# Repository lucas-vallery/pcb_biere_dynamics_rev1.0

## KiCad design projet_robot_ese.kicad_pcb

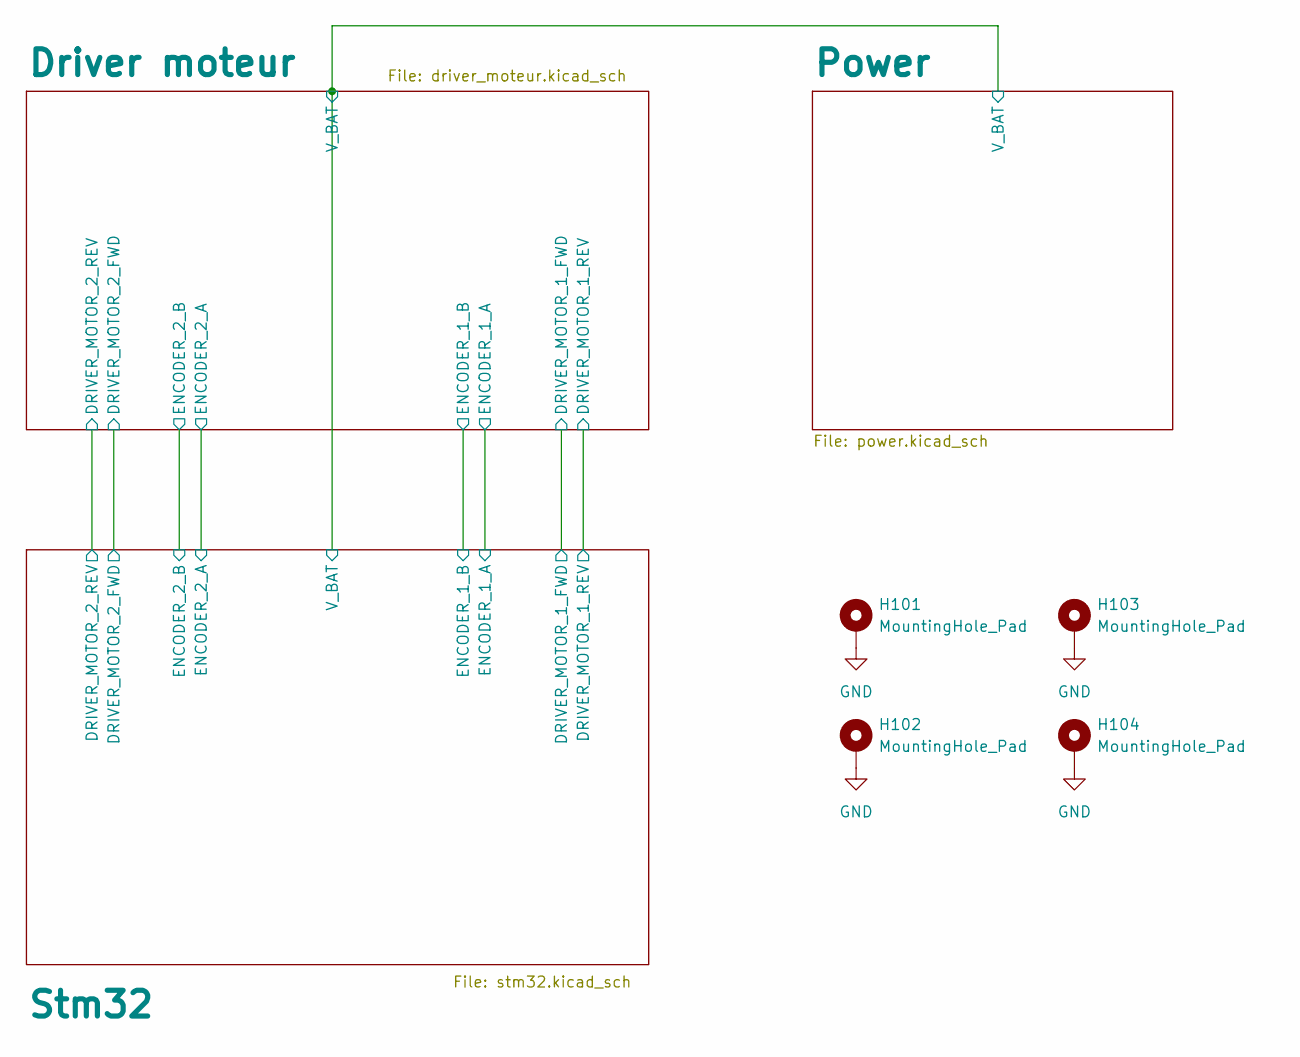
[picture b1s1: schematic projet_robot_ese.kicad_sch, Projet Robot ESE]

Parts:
H101, H102, H103, H104: MountingHole_Pad; MountingHole_3.2mm_M3_Pad_Via

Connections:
GND: H101.1, H102.1, H103.1, H104.1; also elsewhere on the board

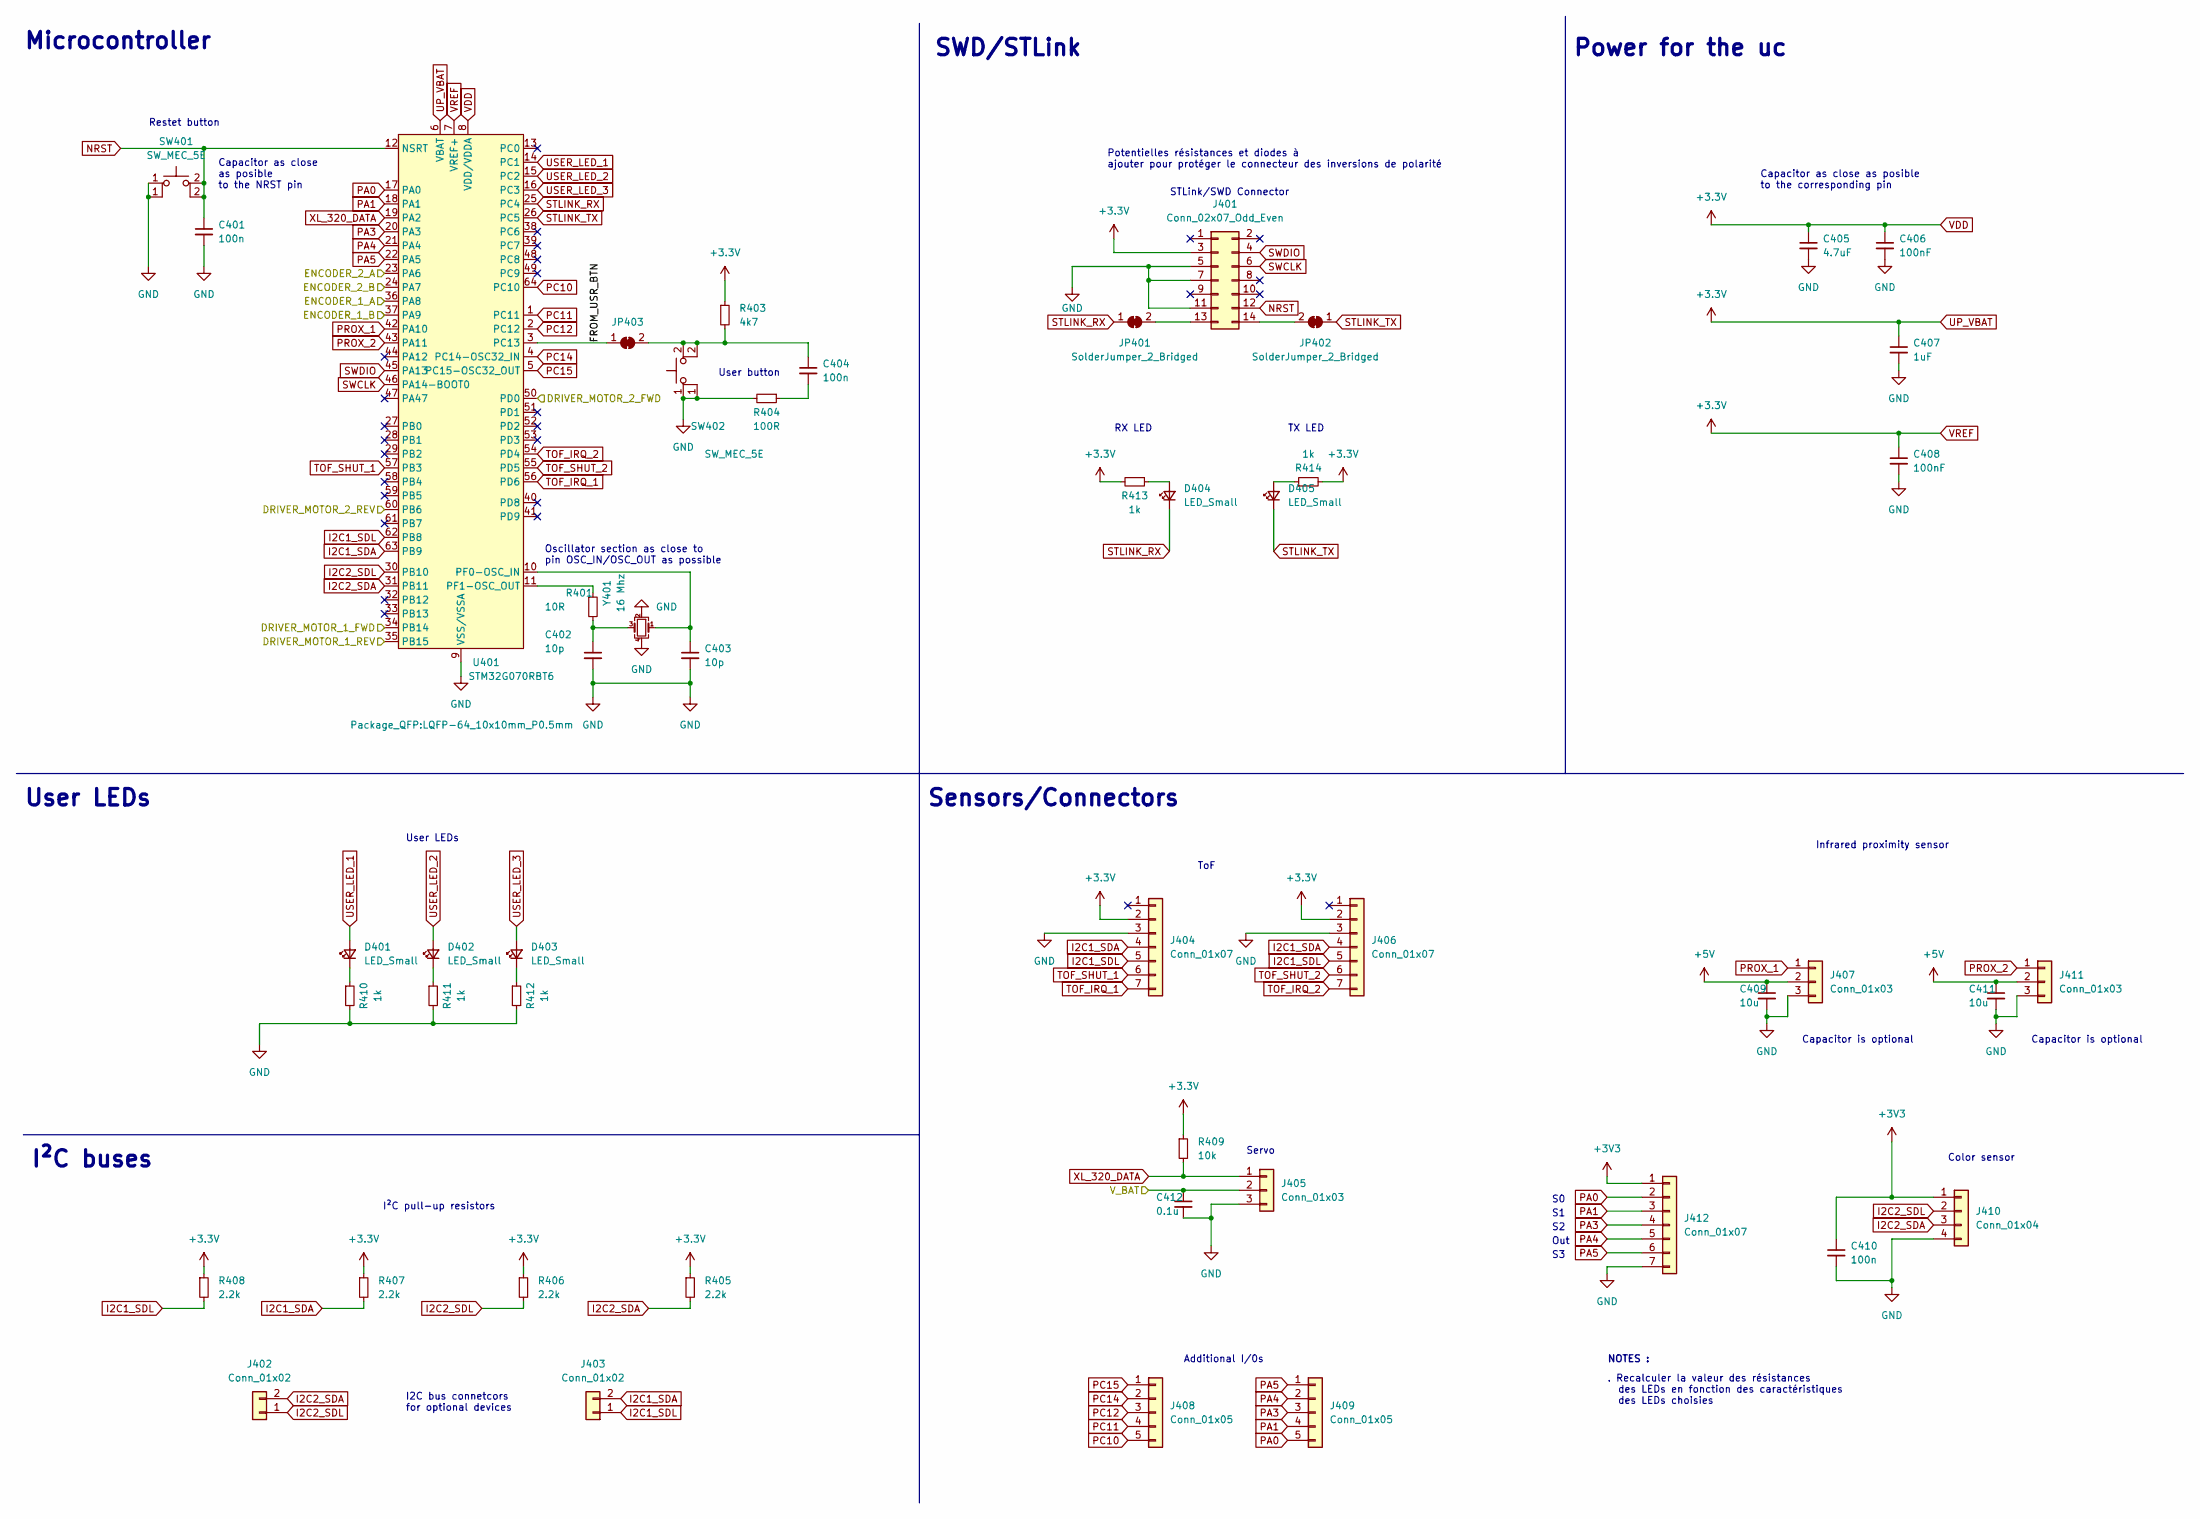
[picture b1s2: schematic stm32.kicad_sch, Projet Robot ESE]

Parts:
C401, C404, C410: 100n; C_0603_1608Metric_Pad1.08x0.95mm_HandSolder
C402, C403: 10p; C_0603_1608Metric_Pad1.08x0.95mm_HandSolder
C405: 4.7uF; C_0603_1608Metric_Pad1.08x0.95mm_HandSolder
C406, C408: 100nF; C_0603_1608Metric_Pad1.08x0.95mm_HandSolder
C407: 1uF; C_0603_1608Metric_Pad1.08x0.95mm_HandSolder
C409, C411: 10u; C_0603_1608Metric_Pad1.08x0.95mm_HandSolder
C412: 0.1u; C_0603_1608Metric_Pad1.08x0.95mm_HandSolder
D401, D402, D403, D404, D405: LED_Small; LED_0603_1608Metric_Pad1.05x0.95mm_HandSolder
J401: Conn_02x07_Odd_Even; PinHeader_2x07_P1.27mm_Vertical_SMD
J402, J403: Conn_01x02; JST_XH_B2B-XH-A_1x02_P2.50mm_Vertical
J404, J406, J412: Conn_01x07; JST_XH_B7B-XH-A_1x07_P2.50mm_Vertical
J405, J407, J411: Conn_01x03; JST_XH_B3B-XH-A_1x03_P2.50mm_Vertical
J408, J409: Conn_01x05; PinSocket_1x05_P2.54mm_Vertical
J410: Conn_01x04; JST_XH_B4B-XH-A_1x04_P2.50mm_Vertical
JP401, JP402, JP403: SolderJumper_2_Bridged; SolderJumper-2_P1.3mm_Bridged_Pad1.0x1.5mm
R401: 10R; R_0603_1608Metric_Pad0.98x0.95mm_HandSolder
R403: 4k7; R_0603_1608Metric_Pad0.98x0.95mm_HandSolder
R404: 100R; R_0603_1608Metric_Pad0.98x0.95mm_HandSolder
R405, R406, R407, R408: 2.2k; R_0603_1608Metric_Pad0.98x0.95mm_HandSolder
R409: 10k; R_0603_1608Metric_Pad0.98x0.95mm_HandSolder
R410, R411, R412, R413, R414: 1k; R_0603_1608Metric_Pad0.98x0.95mm_HandSolder
SW401, SW402: SW_MEC_5E; SW_PUSH_6mm
U401: STM32G070RBT6; LQFP-64_10x10mm_P0.5mm
Y401: 16 Mhz; Crystal_SMD_EuroQuartz_MT-4Pin_3.2x2.5mm

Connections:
+5V: C409.1, C411.1, J407.2, J411.2; also elsewhere on the board
/Driver moteur/DRIVER_MOTOR_1_FWD: U401.34 (PB14); also elsewhere on the board
/Driver moteur/DRIVER_MOTOR_1_REV: U401.35 (PB15); also elsewhere on the board
/Driver moteur/DRIVER_MOTOR_2_FWD: U401.50 (PD0); also elsewhere on the board
/Driver moteur/DRIVER_MOTOR_2_REV: U401.60 (PB6); also elsewhere on the board
/Driver moteur/ENCODER_1_A: U401.36 (PA8); also elsewhere on the board
/Driver moteur/ENCODER_1_B: U401.37 (PA9); also elsewhere on the board
/Driver moteur/ENCODER_2_A: U401.23 (PA6); also elsewhere on the board
/Driver moteur/ENCODER_2_B: U401.24 (PA7); also elsewhere on the board
/Driver moteur/V_BAT: C412.1, J405.2; also elsewhere on the board
/Stm32/FROM_USR_BTN: JP403.1 (A), U401.3 (PC13)
GND: C401.2, C402.2, C403.2, C405.2, C406.2, C407.2, C408.2, C409.2, C410.2, C411.2, C412.2, J401.5, J401.7, J401.11, J404.3, J405.3, J406.3, J407.3, J410.4, J411.3, J412.7, R404.2, R410.2, R411.2, R412.2, SW401.1 (2), SW402.1 (2), U401.9 (VSS/VSSA), Y401.2, Y401.4; also elsewhere on the board
I2C1_SDA: J403.2, J404.4, J406.4, R407.2, U401.63 (PB9)
I2C1_SDL: J403.1, J404.5, J406.5, R408.2, U401.62 (PB8)
I2C2_SDA: J402.2, J410.3, R405.2, U401.31 (PB11)
I2C2_SDL: J402.1, J410.2, R406.2, U401.30 (PB10)
NRST: C401.1, J401.12, SW401.2 (K), U401.12 (NSRT)
unnamed: C402.1, R401.2, Y401.3
unnamed: C403.1, U401.10 (PF0-OSC_IN), Y401.1
unnamed: C404.1, JP403.2 (B), R403.2, SW402.2 (A)
unnamed: C404.2, R404.1
unnamed: D401.1 (K), R410.1
unnamed: D402.1 (K), R411.1
unnamed: D403.1 (K), R412.1
unnamed: D404.2 (A), R413.1
unnamed: D405.2 (A), R414.1
unnamed: J401.13, JP401.2 (B)
unnamed: J401.14, JP402.2 (B)
unnamed: R401.1, U401.11 (PF1-OSC_OUT)
PA0: J409.5, J412.2, U401.17 (PA0)
PA1: J409.4, J412.3, U401.18 (PA1)
PA3: J409.3, J412.4, U401.20 (PA3)
PA4: J409.2, J412.5, U401.21 (PA4)
PA5: J409.1, J412.6, U401.22 (PA5)
PC10: J408.5, U401.64 (PC10)
PC11: J408.4, U401.1 (PC11)
PC12: J408.3, U401.2 (PC12)
PC14: J408.2, U401.4 (PC14-OSC32_IN)
PC15: J408.1, U401.5 (PC15-OSC32_OUT)
PROX_1: J407.1, U401.42 (PA10)
PROX_2: J411.1, U401.43 (PA11)
STLINK_RX: D404.1 (K), JP401.1 (A), U401.25 (PC4)
STLINK_TX: D405.1 (K), JP402.1 (A), U401.26 (PC5)
SWCLK: J401.6, U401.46 (PA14-BOOT0)
SWDIO: J401.4, U401.45 (PA13)
TOF_IRQ_1: J404.7, U401.56 (PD6)
TOF_IRQ_2: J406.7, U401.54 (PD4)
TOF_SHUT_1: J404.6, U401.57 (PB3)
TOF_SHUT_2: J406.6, U401.55 (PD5)
USER_LED_1: D401.2 (A), U401.14 (PC1)
USER_LED_2: D402.2 (A), U401.15 (PC2)
USER_LED_3: D403.2 (A), U401.16 (PC3)
XL_320_DATA: J405.1, R409.2, U401.19 (PA2)

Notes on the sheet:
Capacitor as close as posible to the NRST pin
Capacitor as close as posible to the corresponding pin
Potentielles résistances et diodes à ajouter pour protéger le connecteur des inversions de polarité
User LEDs
I2C bus connetcors for optional devices
Out
SWD/STLink
. Recalculer la valeur des résistances des LEDs en fonction des caractéristiques des LEDs choisies
Restet button
Sensors/Connectors
Capacitor is optional
I²C pull-up resistors
Power for the uc
Oscillator section as close to pin OSC_IN/OSC_OUT as possible
Additional I/0s
Servo
NOTES :
TX LED
I²C buses
Color sensor
RX LED
User button
STLink/SWD Connector
Infrared proximity sensor
ToF
Microcontroller

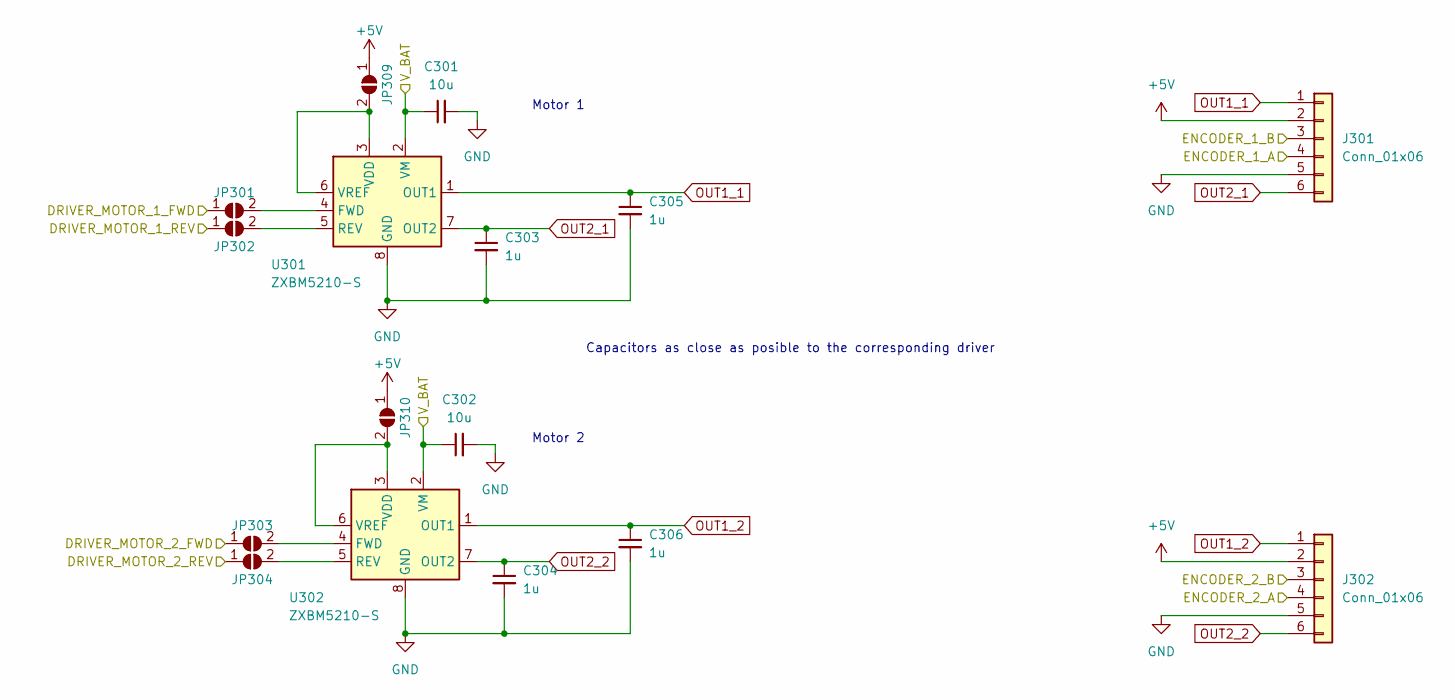
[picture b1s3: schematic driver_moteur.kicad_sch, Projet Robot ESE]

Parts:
C301, C302: 10u; C_0603_1608Metric_Pad1.08x0.95mm_HandSolder
C303, C304, C305, C306: 1u; C_0603_1608Metric_Pad1.08x0.95mm_HandSolder
J301, J302: Conn_01x06; JST_XH_B6B-XH-A_1x06_P2.50mm_Vertical
JP301, JP302, JP303, JP304, JP309, JP310: SolderJumper_2_Open; SolderJumper-2_P1.3mm_Open_TrianglePad1.0x1.5mm
U301, U302: ZXBM5210-S; SOIC-8_3.9x4.9mm_P1.27mm

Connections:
+5V: J301.2, J302.2, JP309.1 (A), JP310.1 (A); also elsewhere on the board
/Driver moteur/DRIVER_MOTOR_1_FWD: JP301.1 (A); also elsewhere on the board
/Driver moteur/DRIVER_MOTOR_1_REV: JP302.1 (A); also elsewhere on the board
/Driver moteur/DRIVER_MOTOR_2_FWD: JP303.1 (A); also elsewhere on the board
/Driver moteur/DRIVER_MOTOR_2_REV: JP304.1 (A); also elsewhere on the board
/Driver moteur/ENCODER_1_A: J301.4; also elsewhere on the board
/Driver moteur/ENCODER_1_B: J301.3; also elsewhere on the board
/Driver moteur/ENCODER_2_A: J302.4; also elsewhere on the board
/Driver moteur/ENCODER_2_B: J302.3; also elsewhere on the board
/Driver moteur/V_BAT: C301.1, C302.1, U301.2 (VM), U302.2 (VM); also elsewhere on the board
GND: C301.2, C302.2, C303.2, C304.2, C305.2, C306.2, J301.5, J302.5, U301.8 (GND), U302.8 (GND); also elsewhere on the board
unnamed: JP301.2 (B), U301.4 (FWD)
unnamed: JP302.2 (B), U301.5 (REV)
unnamed: JP303.2 (B), U302.4 (FWD)
unnamed: JP304.2 (B), U302.5 (REV)
unnamed: JP309.2 (B), U301.3 (VDD), U301.6 (VREF)
unnamed: JP310.2 (B), U302.3 (VDD), U302.6 (VREF)
OUT1_1: C305.1, J301.1, U301.1 (OUT1)
OUT1_2: C306.1, J302.1, U302.1 (OUT1)
OUT2_1: C303.1, J301.6, U301.7 (OUT2)
OUT2_2: C304.1, J302.6, U302.7 (OUT2)

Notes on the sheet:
Capacitors as close as posible to the corresponding driver
Motor 2
Motor 1

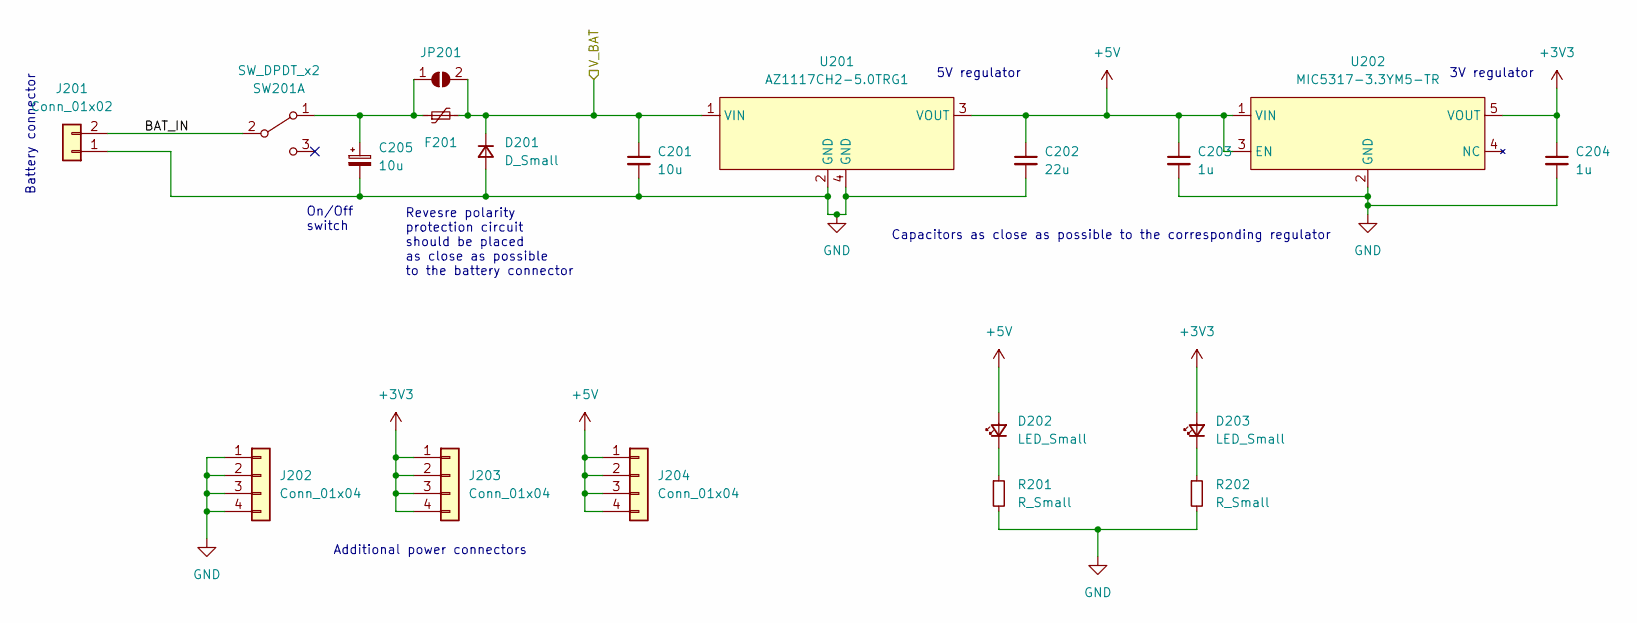
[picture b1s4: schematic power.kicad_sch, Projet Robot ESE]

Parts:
C201: 10u; C_0603_1608Metric_Pad1.08x0.95mm_HandSolder
C202: 22u; C_0603_1608Metric_Pad1.08x0.95mm_HandSolder
C203, C204: 1u; C_0603_1608Metric_Pad1.08x0.95mm_HandSolder
C205: 10u; CP_Radial_D6.3mm_P2.50mm
D201: D_Small; D_0603_1608Metric_Pad1.05x0.95mm_HandSolder
D202, D203: LED_Small; LED_0603_1608Metric_Pad1.05x0.95mm_HandSolder
F201: Polyfuse_Small; Fuse_1206_3216Metric_Pad1.42x1.75mm_HandSolder
J201: Conn_01x02; JST_XH_B2B-XH-A_1x02_P2.50mm_Vertical
J202, J203, J204: Conn_01x04; PinSocket_1x04_P2.54mm_Vertical
JP201: SolderJumper_2_Open; SolderJumper-2_P1.3mm_Open_TrianglePad1.0x1.5mm
R201, R202: R_Small; R_0603_1608Metric_Pad0.98x0.95mm_HandSolder
SW201: SW_DPDT_x2; 1A11-NF5STSE-B
U201: AZ1117CH2-5.0TRG1; SOT-223
U202: MIC5317-3.3YM5-TR; SOT-23-5_HandSoldering

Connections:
+5V: C202.1, C203.1, D202.2 (A), J204.1, J204.2, J204.3, J204.4, U201.3 (VOUT), U202.1 (VIN), U202.3 (EN); also elsewhere on the board
/Driver moteur/V_BAT: C201.1, D201.1 (K), F201.2, JP201.2 (B), U201.1 (VIN); also elsewhere on the board
/Power/BAT_IN: J201.2, SW201.2 (B)
GND: C201.2, C202.2, C203.2, C204.2, C205.2, D201.2 (A), J201.1, J202.1, J202.2, J202.3, J202.4, R201.2, R202.2, U201.2 (GND), U201.4 (GND), U202.2 (GND); also elsewhere on the board
unnamed: C205.1, F201.1, JP201.1 (A), SW201.1 (A)
unnamed: D202.1 (K), R201.1
unnamed: D203.1 (K), R202.1

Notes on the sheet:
Additional power connectors
3V regulator
Revesre polarity protection circuit should be placed as close as possible to the battery connector
On/Off switch
Capacitors as close as possible to the corresponding regulator
Battery connector
5V regulator

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
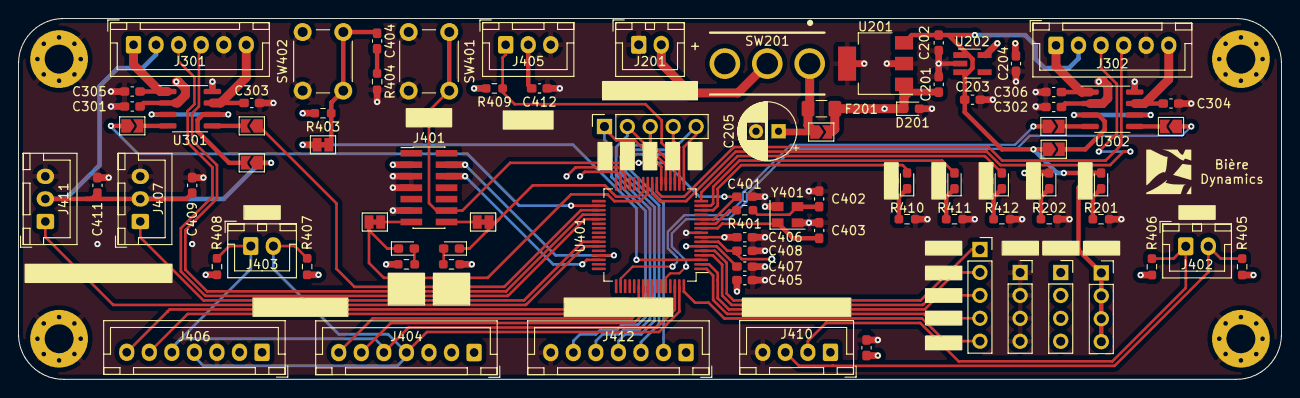
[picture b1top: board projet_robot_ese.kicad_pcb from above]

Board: 4 copper layers, 140.0 x 40.0 mm, 88 parts (0 on the bottom side), 68 nets.

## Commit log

2022-10-21 Last commit
2022-10-21 Prof approved commit
2022-10-21 I2C bus correction & simplifaction
2022-10-21 gerber files update
2022-10-21 Silkscreen update
2022-10-27 Color sensor modif
